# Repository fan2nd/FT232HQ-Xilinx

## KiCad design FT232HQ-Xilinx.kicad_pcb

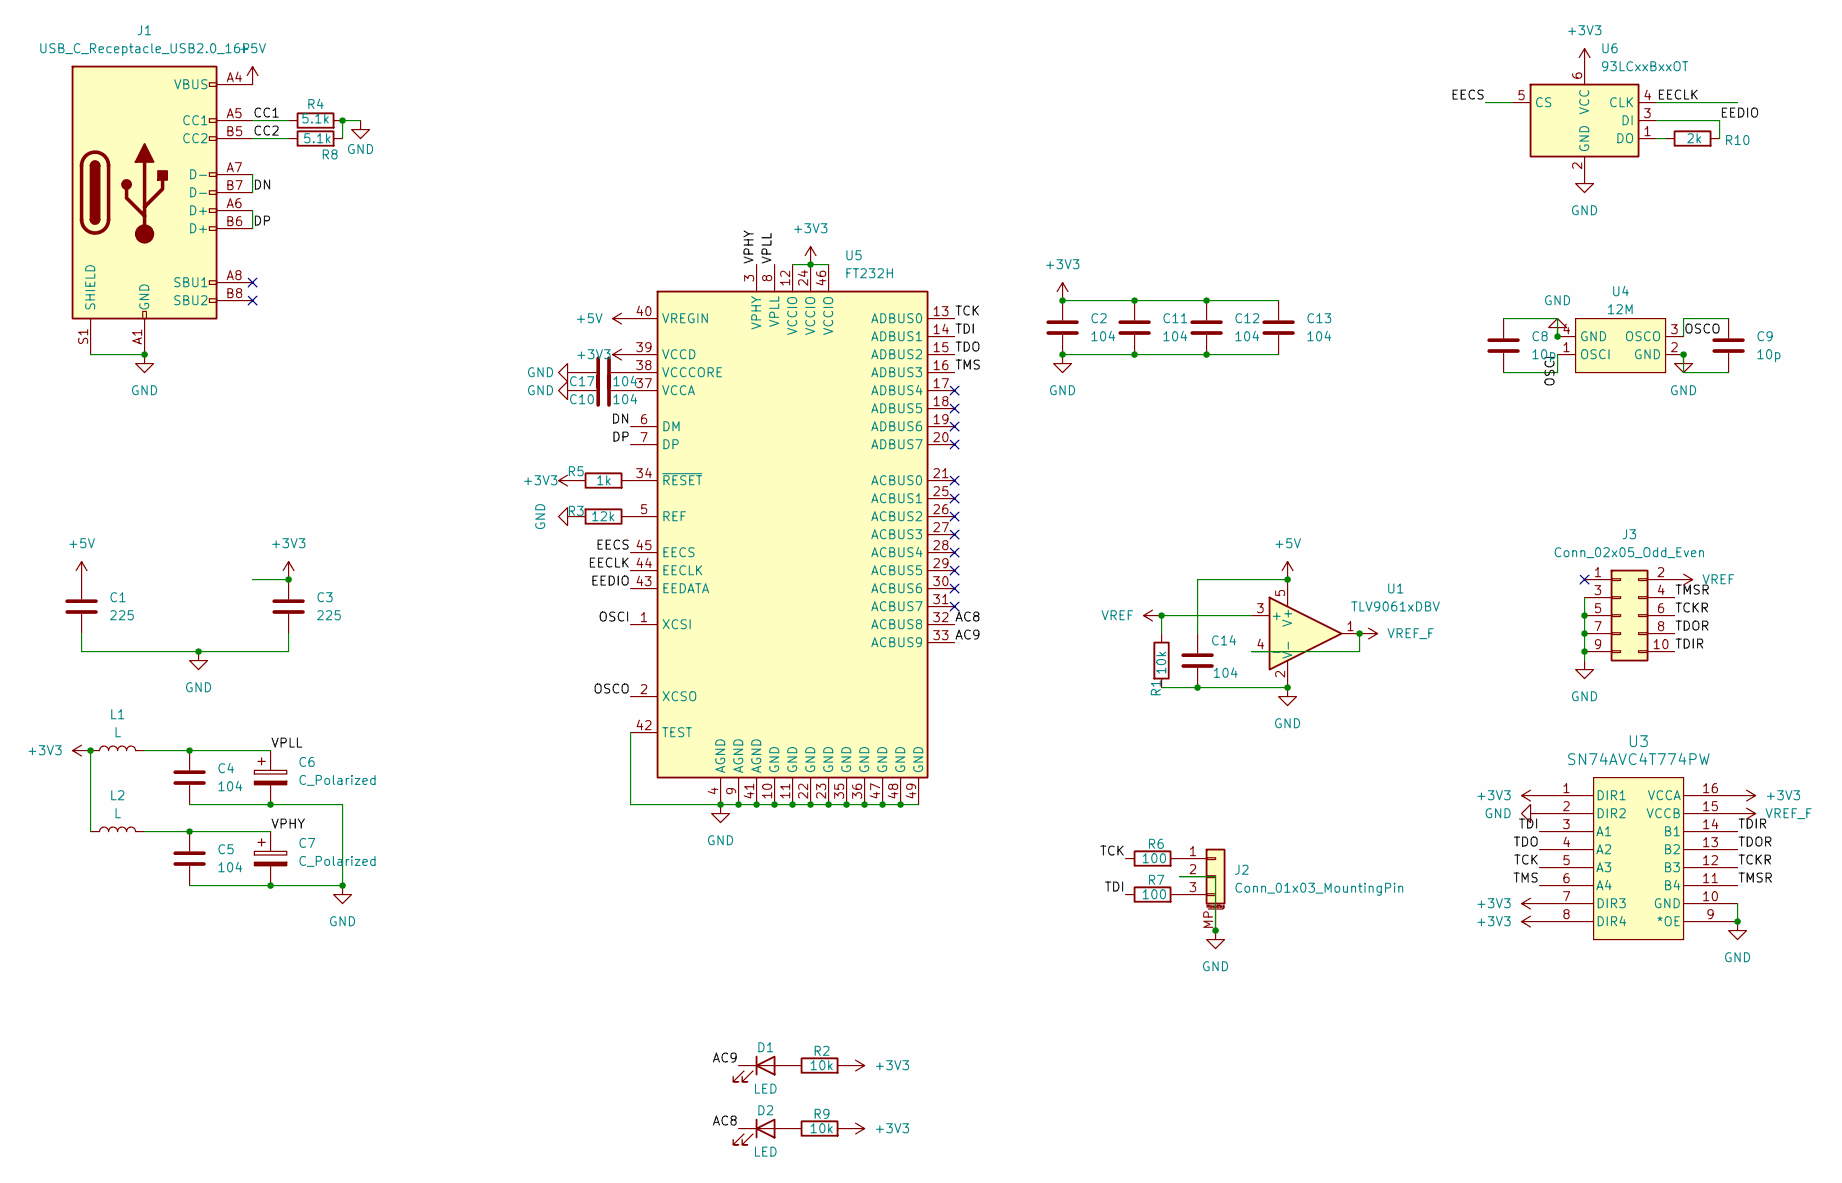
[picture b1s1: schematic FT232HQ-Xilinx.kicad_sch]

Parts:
C1, C3: 225; C_0402_1005Metric
C2, C4, C5, C10, C11, C12, C13, C14, C17: 104; C_0402_1005Metric
C6, C7: C_Polarized; C_0603_1608Metric
C8, C9: 10p; C_0402_1005Metric
D1, D2: LED; LED_0402_1005Metric
J1: USB_C_Receptacle_USB2.0_16P; USB_C_Receptacle_TYPE-C-12P
J2: Conn_01x03_MountingPin; JST_SH_SM03B-SRSS-TB_1x03-1MP_P1.00mm_Horizontal
J3: Conn_02x05_Odd_Even; DC3_02x05_2.54_Odd_Even
L1, L2: L; L_0603_1608Metric
R1, R2, R9: 10k; R_0402_1005Metric
R3: 12k; R_0402_1005Metric
R4, R8: 5.1k; R_0402_1005Metric
R5: 1k; R_0402_1005Metric
R6, R7: 100; R_0402_1005Metric
R10: 2k; R_0402_1005Metric
U1: TLV9061xDBV; SOT-23-5
U3: SN74AVC4T774PW; TSSOP-16_4.4x5mm_P0.65mm
U4: 12M; Oscillator_SMD_13_3.2x2.5mm
U5: FT232H; QFN-48-1EP_8x8mm_P0.5mm_EP6.2x6.2mm
U6: 93LCxxBxxOT; SOT-23-6

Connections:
+3V3: C2.1, C3.1, C11.1, C12.1, C13.1, L1.1, L2.1, R2.2, R5.1, R9.2, U3.1 (DIR1), U3.7 (DIR3), U3.8 (DIR4), U3.16 (VCCA), U5.12 (VCCIO), U5.24 (VCCIO), U5.39 (VCCD), U5.46 (VCCIO), U6.6 (VCC)
+5V: C1.1, C14.1, J1.A4 (VBUS), J1.A9 (VBUS), J1.B4 (VBUS), J1.B9 (VBUS), U1.5 (V+), U5.40 (VREGIN)
/AC8: D2.1 (K), U5.32 (ACBUS8)
/AC9: D1.1 (K), U5.33 (ACBUS9)
/CC1: J1.A5 (CC1), R4.1
/CC2: J1.B5 (CC2), R8.1
/DN: J1.A7 (D-), J1.B7 (D-), U5.6 (DM)
/DP: J1.A6 (D+), J1.B6 (D+), U5.7 (DP)
/EECLK: U5.44 (EECLK), U6.4 (CLK)
/EECS: U5.45 (EECS), U6.5 (CS)
/EEDIO: R10.2, U5.43 (EEDATA), U6.3 (DI)
/OSCI: C8.2, U4.1 (OSCI), U5.1 (XCSI)
/OSCO: C9.2, U4.3 (OSCO), U5.2 (XCSO)
/TCK: R6.1, U3.5 (A3), U5.13 (ADBUS0)
/TCKR: J3.6, U3.12 (B3)
/TDI: R7.1, U3.3 (A1), U5.14 (ADBUS1)
/TDIR: J3.10, U3.14 (B1)
/TDO: U3.4 (A2), U5.15 (ADBUS2)
/TDOR: J3.8, U3.13 (B2)
/TMS: U3.6 (A4), U5.16 (ADBUS3)
/TMSR: J3.4, U3.11 (B4)
/VPHY: C5.1, C7.1, L2.2, U5.3 (VPHY)
/VPLL: C4.1, C6.1, L1.2, U5.8 (VPLL)
GND: C1.2, C2.2, C3.2, C4.2, C5.2, C6.2, C7.2, C8.1, C9.1, C10.1, C11.2, C12.2, C13.2, C14.2, C17.1, J1.A1 (GND), J1.A12 (GND), J1.B1 (GND), J1.B12 (GND), J1.S1 (SHIELD), J2.2, J2.MP (MountPin), J3.3, J3.5, J3.7, J3.9, R1.2, R3.2, R4.2, R8.2, U1.2 (V-), U3.2 (DIR2), U3.9 (*OE), U3.10 (GND), U4.2 (GND), U4.4 (GND), U5.4 (AGND), U5.9 (AGND), U5.10 (GND), U5.11 (GND), U5.22 (GND), U5.23 (GND), U5.35 (GND), U5.36 (GND), U5.41 (AGND), U5.42 (TEST), U5.47 (GND), U5.48 (GND), U5.49 (GND), U6.2 (GND)
unnamed: D1.2 (A), R2.1
unnamed: D2.2 (A), R9.1
unnamed: J2.1, R6.2
unnamed: J2.3, R7.2
unnamed: R3.1, U5.5 (REF)
unnamed: C10.2, U5.37 (VCCA)
unnamed: C17.2, U5.38 (VCCCORE)
unnamed: R5.2, U5.34 (~RESET)
unnamed: R10.1, U6.1 (DO)
VREF: J3.2, R1.1, U1.3 (+)
VREF_F: U1.1, U1.4 (-), U3.15 (VCCB)

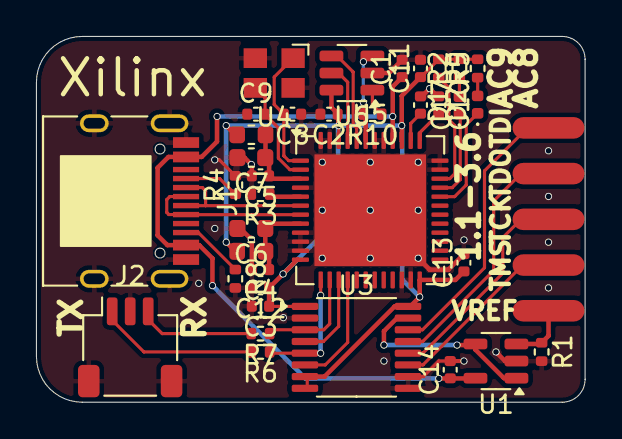
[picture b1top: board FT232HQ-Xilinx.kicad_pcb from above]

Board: 2 copper layers, 30.5 x 20.3 mm, 37 parts (1 on the bottom side), 35 nets.

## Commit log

2024-12-30 init
2025-01-07 fix: 1. Add 10k between vref and gnd. 2. Remove vias on pads.
2025-01-07 fix: c13 drc error
2025-02-17 modified: .gitignore
2025-02-26 update gitignore
2025-02-27 set ac9 as SLEEP# LED
2025-02-28 remove ldo and useless resistance
2025-02-28 little fix
2025-02-28 add raspberry jst-sh1.0 uart
2025-02-28 add text
